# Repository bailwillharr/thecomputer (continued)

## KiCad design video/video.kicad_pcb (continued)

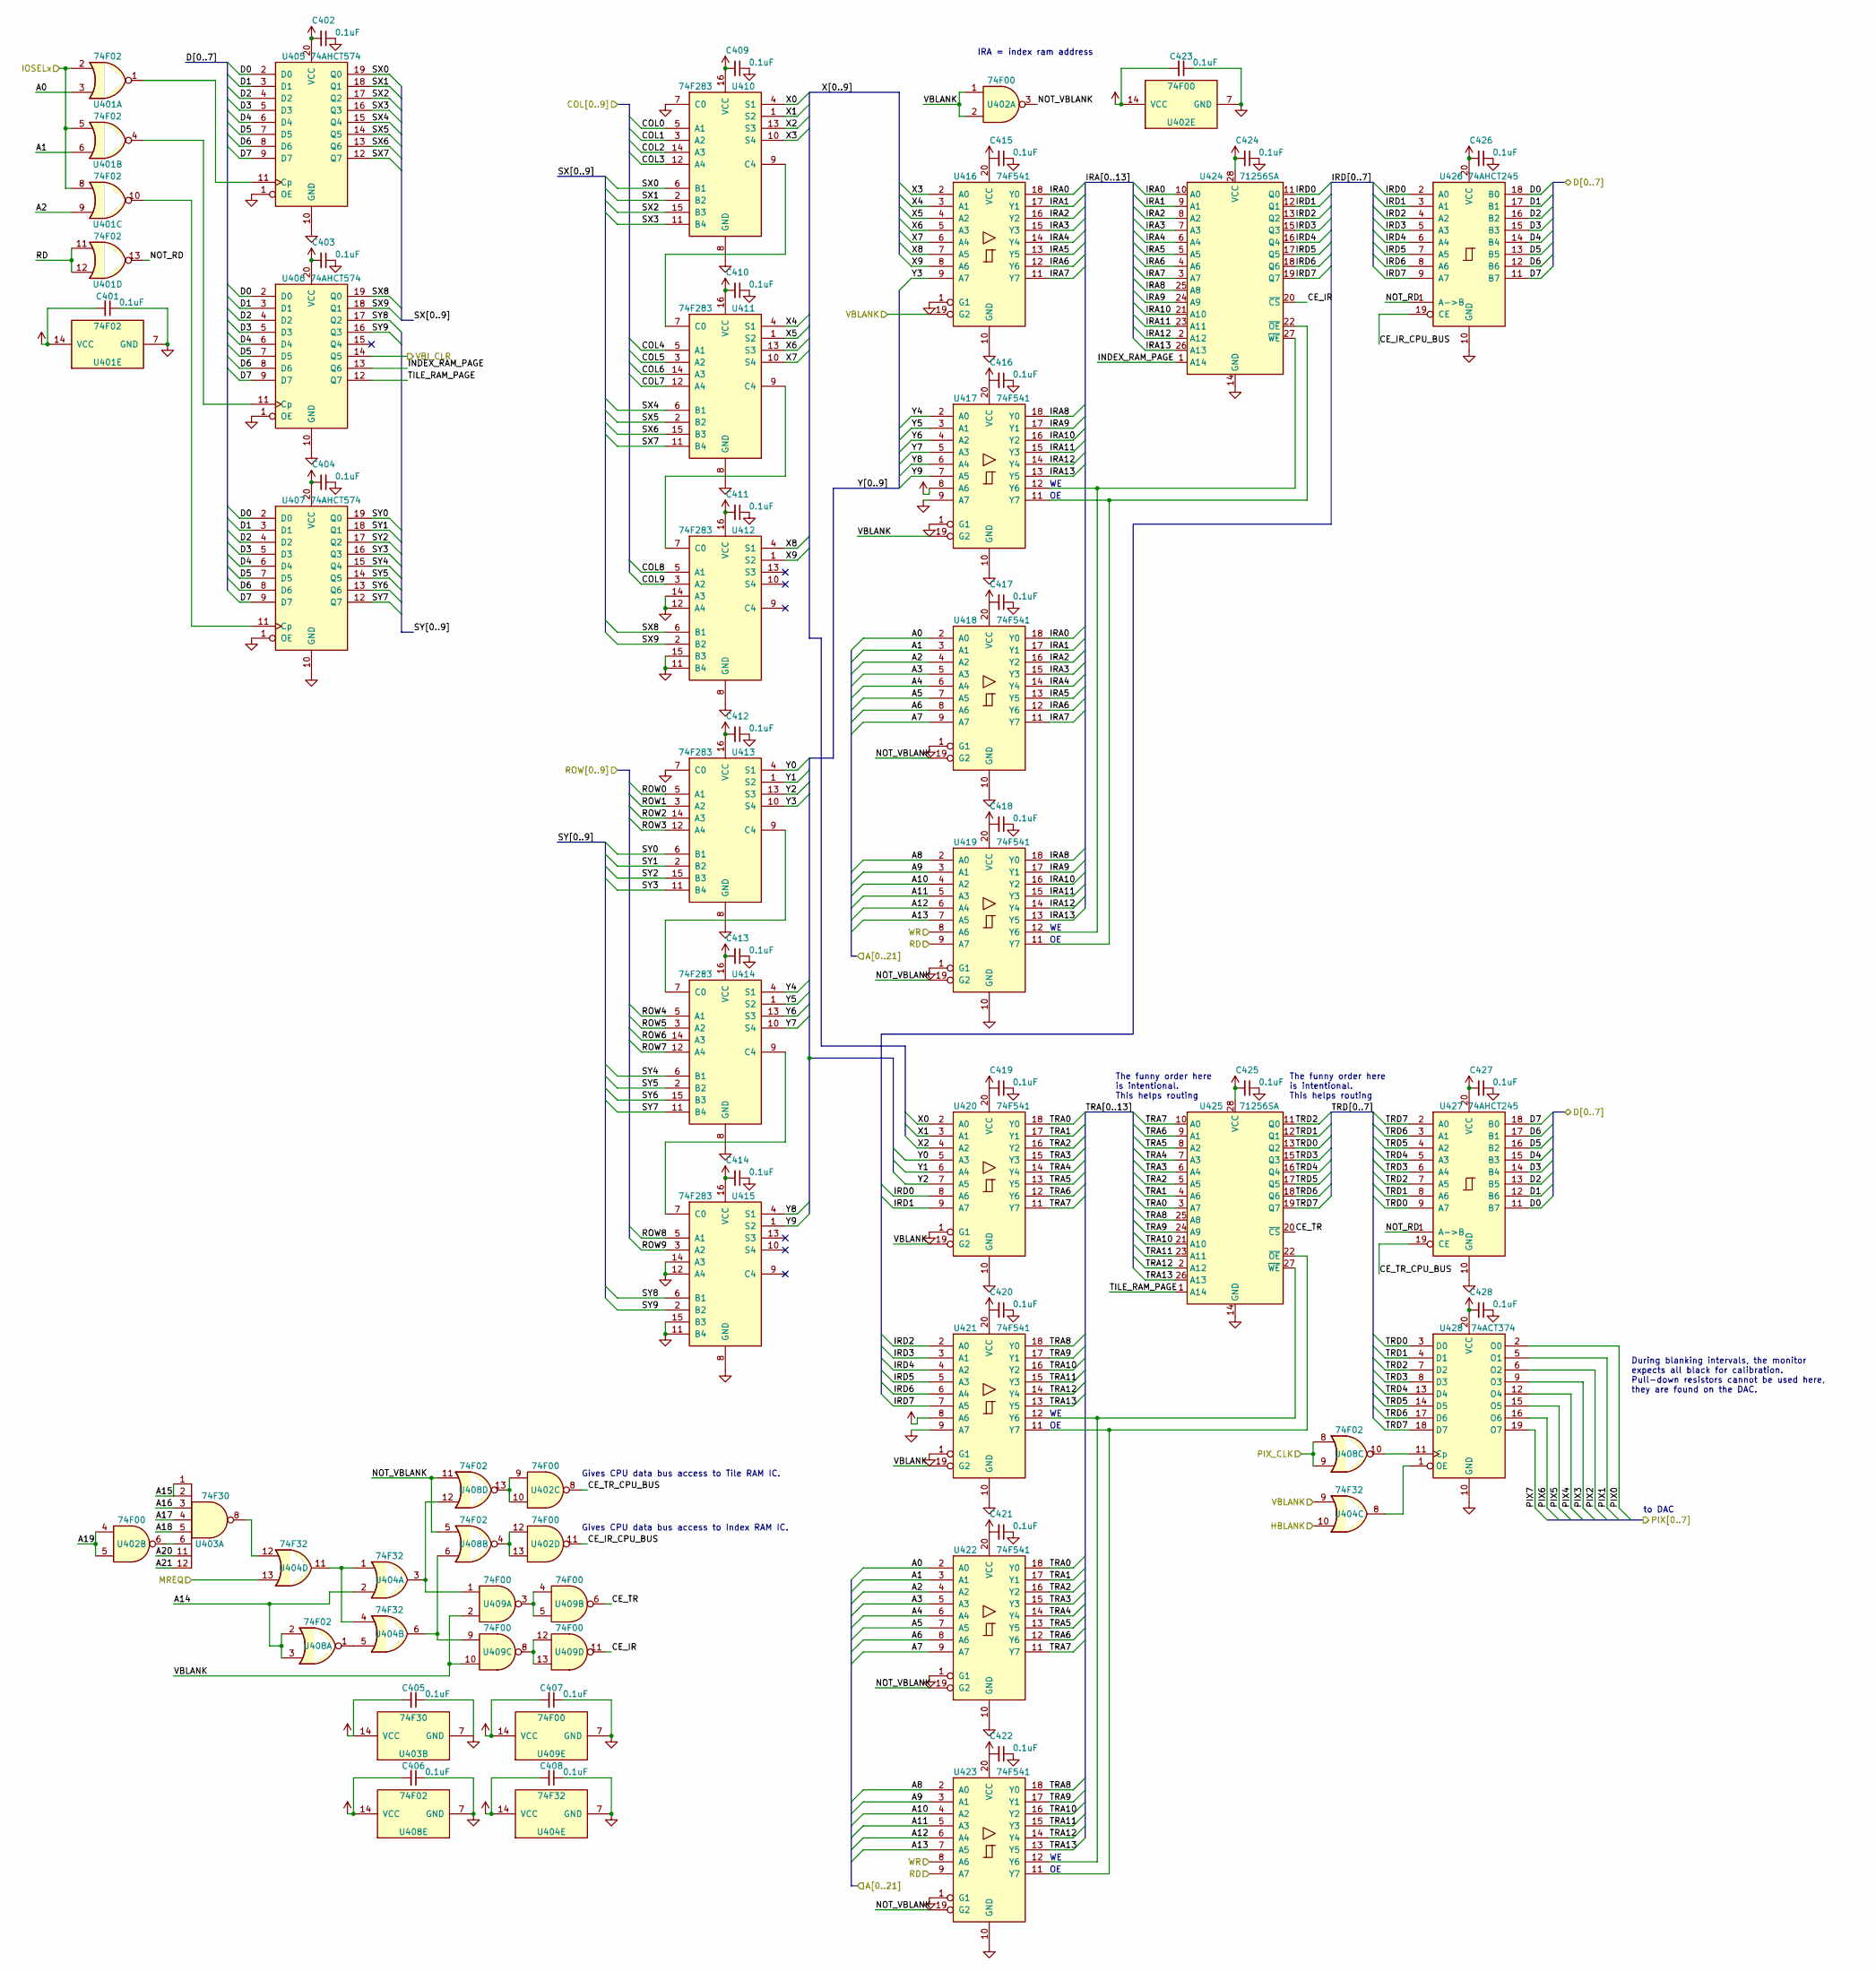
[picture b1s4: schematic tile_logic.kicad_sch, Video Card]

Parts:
C401, C402, C403, C404, C405, C406, C407, C408, C409, C410, C411, C412, C413, C414, C415, C416, C417, C418, C419, C420, C421, C422, C423, C424, C425, C426, C427, C428: 0.1uF; C_Disc_D5.0mm_W2.5mm_P2.50mm; Digikey Part No. 399-9859-1-ND
U401, U408: 74F02; DIP-14_W7.62mm_Socket; Digikey Part No. 296-3541-5-ND
U402, U409: 74F00; DIP-14_W7.62mm_Socket; Digikey Part No. 296-3539-5-ND
U403: 74F30; DIP-14_W7.62mm_Socket; Digikey Part No. 296-SN74F30N-ND
U404: 74F32; DIP-14_W7.62mm_Socket; Digikey Part No. 296-3583-5-ND
U405, U406, U407: 74AHCT574; DIP-20_W7.62mm_Socket; Digikey Part No. 296-4763-5-ND
U410, U411, U412, U413, U414, U415: 74F283; DIP-16_W7.62mm_Socket; Digikey Part No. 296-3580-5-ND
U416, U417, U418, U419, U420, U421, U422, U423: 74F541; DIP-20_W7.62mm_Socket; Digikey Part No. 296-3594-5-ND
U424, U425: 71256SA; DIP-28_W7.62mm_Socket; Digikey Part No. 800-3675-ND
U426, U427: 74AHCT245; DIP-20_W7.62mm_Socket; Digikey Part No. 296-1476-5-ND
U428: 74ACT374; DIP-20_W7.62mm_Socket; Digikey Part No. 296-33658-5-ND

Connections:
+5V: C401.2, C402.2, C403.2, C404.2, C405.2, C406.2, C407.2, C408.2, C409.2, C410.2, C411.2, C412.2, C413.2, C414.2, C415.2, C416.2, C417.2, C418.2, C419.2, C420.2, C421.2, C422.2, C423.2, C424.2, C425.2, C426.2, C427.2, C428.2, U401.14 (VCC), U402.14 (VCC), U403.14 (VCC), U404.14 (VCC), U405.20 (VCC), U406.20 (VCC), U407.20 (VCC), U408.14 (VCC), U409.14 (VCC), U410.16 (VCC), U411.16 (VCC), U412.16 (VCC), U413.16 (VCC), U414.16 (VCC), U415.16 (VCC), U416.20 (VCC), U417.8 (A6), U417.20 (VCC), U418.20 (VCC), U419.20 (VCC), U420.20 (VCC), U421.8 (A6), U421.20 (VCC), U422.20 (VCC), U423.20 (VCC), U424.28 (VCC), U425.28 (VCC), U426.20 (VCC), U427.20 (VCC), U428.20 (VCC); also elsewhere on the board
/A0: U401.3, U418.2 (A0), U422.2 (A0); also elsewhere on the board
/A1: U401.6, U418.3 (A1), U422.3 (A1); also elsewhere on the board
/A2: U401.9, U418.4 (A2), U422.4 (A2); also elsewhere on the board
/A3: U418.5 (A3), U422.5 (A3); also elsewhere on the board
/A4: U418.6 (A4), U422.6 (A4); also elsewhere on the board
/A5: U418.7 (A5), U422.7 (A5); also elsewhere on the board
/A6: U418.8 (A6), U422.8 (A6); also elsewhere on the board
/A7: U418.9 (A7), U422.9 (A7); also elsewhere on the board
/A8: U419.2 (A0), U423.2 (A0); also elsewhere on the board
/A9: U419.3 (A1), U423.3 (A1); also elsewhere on the board
/A10: U419.4 (A2), U423.4 (A2); also elsewhere on the board
/A11: U419.5 (A3), U423.5 (A3); also elsewhere on the board
/A12: U419.6 (A4), U423.6 (A4); also elsewhere on the board
/A13: U419.7 (A5), U423.7 (A5); also elsewhere on the board
/A14: U404.2, U408.2, U408.3; also elsewhere on the board
/A15: U403.1, U403.2; also elsewhere on the board
/A16: U403.3; also elsewhere on the board
/A17: U403.4; also elsewhere on the board
/A18: U403.5; also elsewhere on the board
/A19: U402.4, U402.5; also elsewhere on the board
/A20: U403.11; also elsewhere on the board
/A21: U403.12; also elsewhere on the board
/D0: U405.2 (D0), U406.2 (D0), U407.2 (D0), U426.18 (B0), U427.11 (B7); also elsewhere on the board
/D1: U405.3 (D1), U406.3 (D1), U407.3 (D1), U426.17 (B1), U427.12 (B6); also elsewhere on the board
/D2: U405.4 (D2), U406.4 (D2), U407.4 (D2), U426.16 (B2), U427.13 (B5); also elsewhere on the board
/D3: U405.5 (D3), U406.5 (D3), U407.5 (D3), U426.15 (B3), U427.14 (B4); also elsewhere on the board
/D4: U405.6 (D4), U406.6 (D4), U407.6 (D4), U426.14 (B4), U427.15 (B3); also elsewhere on the board
/D5: U405.7 (D5), U406.7 (D5), U407.7 (D5), U426.13 (B5), U427.16 (B2); also elsewhere on the board
/D6: U405.8 (D6), U406.8 (D6), U407.8 (D6), U426.12 (B6), U427.17 (B1); also elsewhere on the board
/D7: U405.9 (D7), U406.9 (D7), U407.9 (D7), U426.11 (B7), U427.18 (B0); also elsewhere on the board
/IOSELx: U401.2, U401.5, U401.8; also elsewhere on the board
/MREQ: U404.13; also elsewhere on the board
/PIX0: U428.2 (O0); also elsewhere on the board
/PIX1: U428.5 (O1); also elsewhere on the board
/PIX2: U428.6 (O2); also elsewhere on the board
/PIX3: U428.9 (O3); also elsewhere on the board
/PIX4: U428.12 (O4); also elsewhere on the board
/PIX5: U428.15 (O5); also elsewhere on the board
/PIX6: U428.16 (O6); also elsewhere on the board
/PIX7: U428.19 (O7); also elsewhere on the board
/PIX_CLK: U408.8, U408.9; also elsewhere on the board
/RD: U401.11, U401.12, U419.9 (A7), U423.9 (A7); also elsewhere on the board
/TILE_LOGIC/CE_IR: U409.11, U424.20 (~CS)
/TILE_LOGIC/CE_IR_CPU_BUS: U402.11, U426.19 (CE)
/TILE_LOGIC/CE_TR: U409.6, U425.20 (~CS)
/TILE_LOGIC/CE_TR_CPU_BUS: U402.8, U427.19 (CE)
/TILE_LOGIC/HBLANK: U404.10; also elsewhere on the board
/TILE_LOGIC/INDEX_RAM_PAGE: U406.13 (Q6), U424.1 (A14)
/TILE_LOGIC/IRA0: U416.18 (Y0), U418.18 (Y0), U424.10 (A0)
/TILE_LOGIC/IRA1: U416.17 (Y1), U418.17 (Y1), U424.9 (A1)
/TILE_LOGIC/IRA2: U416.16 (Y2), U418.16 (Y2), U424.8 (A2)
/TILE_LOGIC/IRA3: U416.15 (Y3), U418.15 (Y3), U424.7 (A3)
/TILE_LOGIC/IRA4: U416.14 (Y4), U418.14 (Y4), U424.6 (A4)
/TILE_LOGIC/IRA5: U416.13 (Y5), U418.13 (Y5), U424.5 (A5)
/TILE_LOGIC/IRA6: U416.12 (Y6), U418.12 (Y6), U424.4 (A6)
/TILE_LOGIC/IRA7: U416.11 (Y7), U418.11 (Y7), U424.3 (A7)
/TILE_LOGIC/IRA8: U417.18 (Y0), U419.18 (Y0), U424.25 (A8)
/TILE_LOGIC/IRA9: U417.17 (Y1), U419.17 (Y1), U424.24 (A9)
/TILE_LOGIC/IRA10: U417.16 (Y2), U419.16 (Y2), U424.21 (A10)
/TILE_LOGIC/IRA11: U417.15 (Y3), U419.15 (Y3), U424.23 (A11)
/TILE_LOGIC/IRA12: U417.14 (Y4), U419.14 (Y4), U424.2 (A12)
/TILE_LOGIC/IRA13: U417.13 (Y5), U419.13 (Y5), U424.26 (A13)
/TILE_LOGIC/IRD0: U420.8 (A6), U424.11 (Q0), U426.2 (A0)
/TILE_LOGIC/IRD1: U420.9 (A7), U424.12 (Q1), U426.3 (A1)
/TILE_LOGIC/IRD2: U421.2 (A0), U424.13 (Q2), U426.4 (A2)
/TILE_LOGIC/IRD3: U421.3 (A1), U424.15 (Q3), U426.5 (A3)
/TILE_LOGIC/IRD4: U421.4 (A2), U424.16 (Q4), U426.6 (A4)
/TILE_LOGIC/IRD5: U421.5 (A3), U424.17 (Q5), U426.7 (A5)
/TILE_LOGIC/IRD6: U421.6 (A4), U424.18 (Q6), U426.8 (A6)
/TILE_LOGIC/IRD7: U421.7 (A5), U424.19 (Q7), U426.9 (A7)
/TILE_LOGIC/NOT_RD: U401.13, U426.1 (A->B), U427.1 (A->B)
/TILE_LOGIC/NOT_VBLANK: U402.3, U408.5, U408.11, U418.19 (G2), U419.19 (G2), U422.19 (G2), U423.19 (G2)
/TILE_LOGIC/SX0: U405.19 (Q0), U410.6 (B1)
/TILE_LOGIC/SX1: U405.18 (Q1), U410.2 (B2)
/TILE_LOGIC/SX2: U405.17 (Q2), U410.15 (B3)
/TILE_LOGIC/SX3: U405.16 (Q3), U410.11 (B4)
/TILE_LOGIC/SX4: U405.15 (Q4), U411.6 (B1)
/TILE_LOGIC/SX5: U405.14 (Q5), U411.2 (B2)
/TILE_LOGIC/SX6: U405.13 (Q6), U411.15 (B3)
/TILE_LOGIC/SX7: U405.12 (Q7), U411.11 (B4)
/TILE_LOGIC/SX8: U406.19 (Q0), U412.6 (B1)
/TILE_LOGIC/SX9: U406.18 (Q1), U412.2 (B2)
/TILE_LOGIC/SY0: U407.19 (Q0), U413.6 (B1)
/TILE_LOGIC/SY1: U407.18 (Q1), U413.2 (B2)
/TILE_LOGIC/SY2: U407.17 (Q2), U413.15 (B3)
/TILE_LOGIC/SY3: U407.16 (Q3), U413.11 (B4)
/TILE_LOGIC/SY4: U407.15 (Q4), U414.6 (B1)
/TILE_LOGIC/SY5: U407.14 (Q5), U414.2 (B2)
/TILE_LOGIC/SY6: U407.13 (Q6), U414.15 (B3)
/TILE_LOGIC/SY7: U407.12 (Q7), U414.11 (B4)
/TILE_LOGIC/SY8: U406.17 (Q2), U415.6 (B1)
/TILE_LOGIC/SY9: U406.16 (Q3), U415.2 (B2)
/TILE_LOGIC/TILE_RAM_PAGE: U406.12 (Q7), U425.1 (A14)
/TILE_LOGIC/TRA0: U420.18 (Y0), U422.18 (Y0), U425.3 (A7)
/TILE_LOGIC/TRA1: U420.17 (Y1), U422.17 (Y1), U425.4 (A6)
/TILE_LOGIC/TRA2: U420.16 (Y2), U422.16 (Y2), U425.5 (A5)
/TILE_LOGIC/TRA3: U420.15 (Y3), U422.15 (Y3), U425.6 (A4)
/TILE_LOGIC/TRA4: U420.14 (Y4), U422.14 (Y4), U425.7 (A3)
/TILE_LOGIC/TRA5: U420.13 (Y5), U422.13 (Y5), U425.8 (A2)
/TILE_LOGIC/TRA6: U420.12 (Y6), U422.12 (Y6), U425.9 (A1)
/TILE_LOGIC/TRA7: U420.11 (Y7), U422.11 (Y7), U425.10 (A0)
/TILE_LOGIC/TRA8: U421.18 (Y0), U423.18 (Y0), U425.25 (A8)
/TILE_LOGIC/TRA9: U421.17 (Y1), U423.17 (Y1), U425.24 (A9)
/TILE_LOGIC/TRA10: U421.16 (Y2), U423.16 (Y2), U425.21 (A10)
/TILE_LOGIC/TRA11: U421.15 (Y3), U423.15 (Y3), U425.23 (A11)
/TILE_LOGIC/TRA12: U421.14 (Y4), U423.14 (Y4), U425.2 (A12)
/TILE_LOGIC/TRA13: U421.13 (Y5), U423.13 (Y5), U425.26 (A13)
/TILE_LOGIC/TRD0: U425.13 (Q2), U427.9 (A7), U428.3 (D0)
/TILE_LOGIC/TRD1: U425.12 (Q1), U427.8 (A6), U428.4 (D1)
/TILE_LOGIC/TRD2: U425.11 (Q0), U427.7 (A5), U428.7 (D2)
/TILE_LOGIC/TRD3: U425.15 (Q3), U427.6 (A4), U428.8 (D3)
/TILE_LOGIC/TRD4: U425.16 (Q4), U427.5 (A3), U428.13 (D4)
/TILE_LOGIC/TRD5: U425.17 (Q5), U427.4 (A2), U428.14 (D5)
/TILE_LOGIC/TRD6: U425.18 (Q6), U427.3 (A1), U428.17 (D6)
/TILE_LOGIC/TRD7: U425.19 (Q7), U427.2 (A0), U428.18 (D7)
/TILE_LOGIC/VBI_CLR: U406.14 (Q5); also elsewhere on the board
/TILE_LOGIC/VBLANK: U402.1, U402.2, U404.9, U409.2, U409.10, U416.19 (G2), U417.19 (G2), U420.19 (G2), U421.19 (G2); also elsewhere on the board
/TILE_LOGIC/X0: U410.4 (S1), U420.2 (A0)
/TILE_LOGIC/X1: U410.1 (S2), U420.3 (A1)
/TILE_LOGIC/X2: U410.13 (S3), U420.4 (A2)
/TILE_LOGIC/X3: U410.10 (S4), U416.2 (A0)
/TILE_LOGIC/X4: U411.4 (S1), U416.3 (A1)
/TILE_LOGIC/X5: U411.1 (S2), U416.4 (A2)
/TILE_LOGIC/X6: U411.13 (S3), U416.5 (A3)
/TILE_LOGIC/X7: U411.10 (S4), U416.6 (A4)
/TILE_LOGIC/X8: U412.4 (S1), U416.7 (A5)
/TILE_LOGIC/X9: U412.1 (S2), U416.8 (A6)
/TILE_LOGIC/Y0: U413.4 (S1), U420.5 (A3)
/TILE_LOGIC/Y1: U413.1 (S2), U420.6 (A4)
/TILE_LOGIC/Y2: U413.13 (S3), U420.7 (A5)
/TILE_LOGIC/Y3: U413.10 (S4), U416.9 (A7)
/TILE_LOGIC/Y4: U414.4 (S1), U417.2 (A0)
/TILE_LOGIC/Y5: U414.1 (S2), U417.3 (A1)
/TILE_LOGIC/Y6: U414.13 (S3), U417.4 (A2)
/TILE_LOGIC/Y7: U414.10 (S4), U417.5 (A3)
/TILE_LOGIC/Y8: U415.4 (S1), U417.6 (A4)
/TILE_LOGIC/Y9: U415.1 (S2), U417.7 (A5)
/TIMING/COL0: U410.5 (A1); also elsewhere on the board
/TIMING/COL1: U410.3 (A2); also elsewhere on the board
/TIMING/COL2: U410.14 (A3); also elsewhere on the board
/TIMING/COL3: U410.12 (A4); also elsewhere on the board
/TIMING/COL4: U411.5 (A1); also elsewhere on the board
/TIMING/COL5: U411.3 (A2); also elsewhere on the board
/TIMING/COL6: U411.14 (A3); also elsewhere on the board
/TIMING/COL7: U411.12 (A4); also elsewhere on the board
/TIMING/COL8: U412.5 (A1); also elsewhere on the board
/TIMING/COL9: U412.3 (A2); also elsewhere on the board
/TIMING/ROW0: U413.5 (A1); also elsewhere on the board
/TIMING/ROW1: U413.3 (A2); also elsewhere on the board
/TIMING/ROW2: U413.14 (A3); also elsewhere on the board
/TIMING/ROW3: U413.12 (A4); also elsewhere on the board
/TIMING/ROW4: U414.5 (A1); also elsewhere on the board
/TIMING/ROW5: U414.3 (A2); also elsewhere on the board
/TIMING/ROW6: U414.14 (A3); also elsewhere on the board
/TIMING/ROW7: U414.12 (A4); also elsewhere on the board
/TIMING/ROW8: U415.5 (A1); also elsewhere on the board
/TIMING/ROW9: U415.3 (A2); also elsewhere on the board
/WR: U419.8 (A6), U423.8 (A6); also elsewhere on the board
GND: C401.1, C402.1, C403.1, C404.1, C405.1, C406.1, C407.1, C408.1, C409.1, C410.1, C411.1, C412.1, C413.1, C414.1, C415.1, C416.1, C417.1, C418.1, C419.1, C420.1, C421.1, C422.1, C423.1, C424.1, C425.1, C426.1, C427.1, C428.1, U401.7 (GND), U402.7 (GND), U403.7 (GND), U404.7 (GND), U405.1 (OE), U405.10 (GND), U406.1 (OE), U406.10 (GND), U407.1 (OE), U407.10 (GND), U408.7 (GND), U409.7 (GND), U410.7 (C0), U410.8 (GND), U411.8 (GND), U412.8 (GND), U412.11 (B4), U412.12 (A4), U412.14 (A3), U412.15 (B3), U413.7 (C0), U413.8 (GND), U414.8 (GND), U415.8 (GND), U415.11 (B4), U415.12 (A4), U415.14 (A3), U415.15 (B3), U416.1 (G1), U416.10 (GND), U417.1 (G1), U417.9 (A7), U417.10 (GND), U418.1 (G1), U418.10 (GND), U419.1 (G1), U419.10 (GND), U420.1 (G1), U420.10 (GND), U421.1 (G1), U421.9 (A7), U421.10 (GND), U422.1 (G1), U422.10 (GND), U423.1 (G1), U423.10 (GND), U424.14 (GND), U425.14 (GND), U426.10 (GND), U427.10 (GND), U428.10 (GND); also elsewhere on the board
unnamed: U402.6, U403.6
unnamed: U402.9, U402.10, U408.13
unnamed: U402.12, U402.13, U408.4
unnamed: U403.8, U404.12
unnamed: U404.1, U404.4, U404.11
unnamed: U404.3, U408.12, U409.1
unnamed: U404.5, U408.1
unnamed: U404.6, U408.6, U409.9
unnamed: U401.1, U405.11 (Cp)
unnamed: U401.4, U406.11 (Cp)
unnamed: U401.10, U407.11 (Cp)
unnamed: U409.3, U409.4, U409.5
unnamed: U409.8, U409.12, U409.13
unnamed: U410.9 (C4), U411.7 (C0)
unnamed: U411.9 (C4), U412.7 (C0)
unnamed: U413.9 (C4), U414.7 (C0)
unnamed: U414.9 (C4), U415.7 (C0)
unnamed: U417.12 (Y6), U419.12 (Y6), U424.27 (~WE)
unnamed: U417.11 (Y7), U419.11 (Y7), U424.22 (~OE)
unnamed: U421.12 (Y6), U423.12 (Y6), U425.27 (~WE)
unnamed: U421.11 (Y7), U423.11 (Y7), U425.22 (~OE)
unnamed: U408.10, U428.11 (Cp)
unnamed: U404.8, U428.1 (OE)

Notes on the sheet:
During blanking intervals, the monitor expects all black for calibration. Pull-down resistors cannot be used here, they are found on the DAC.
to DAC
The funny order here is intentional. This helps routing
Gives CPU data bus access to Index RAM IC.
IRA = index ram address
Gives CPU data bus access to Tile RAM IC.

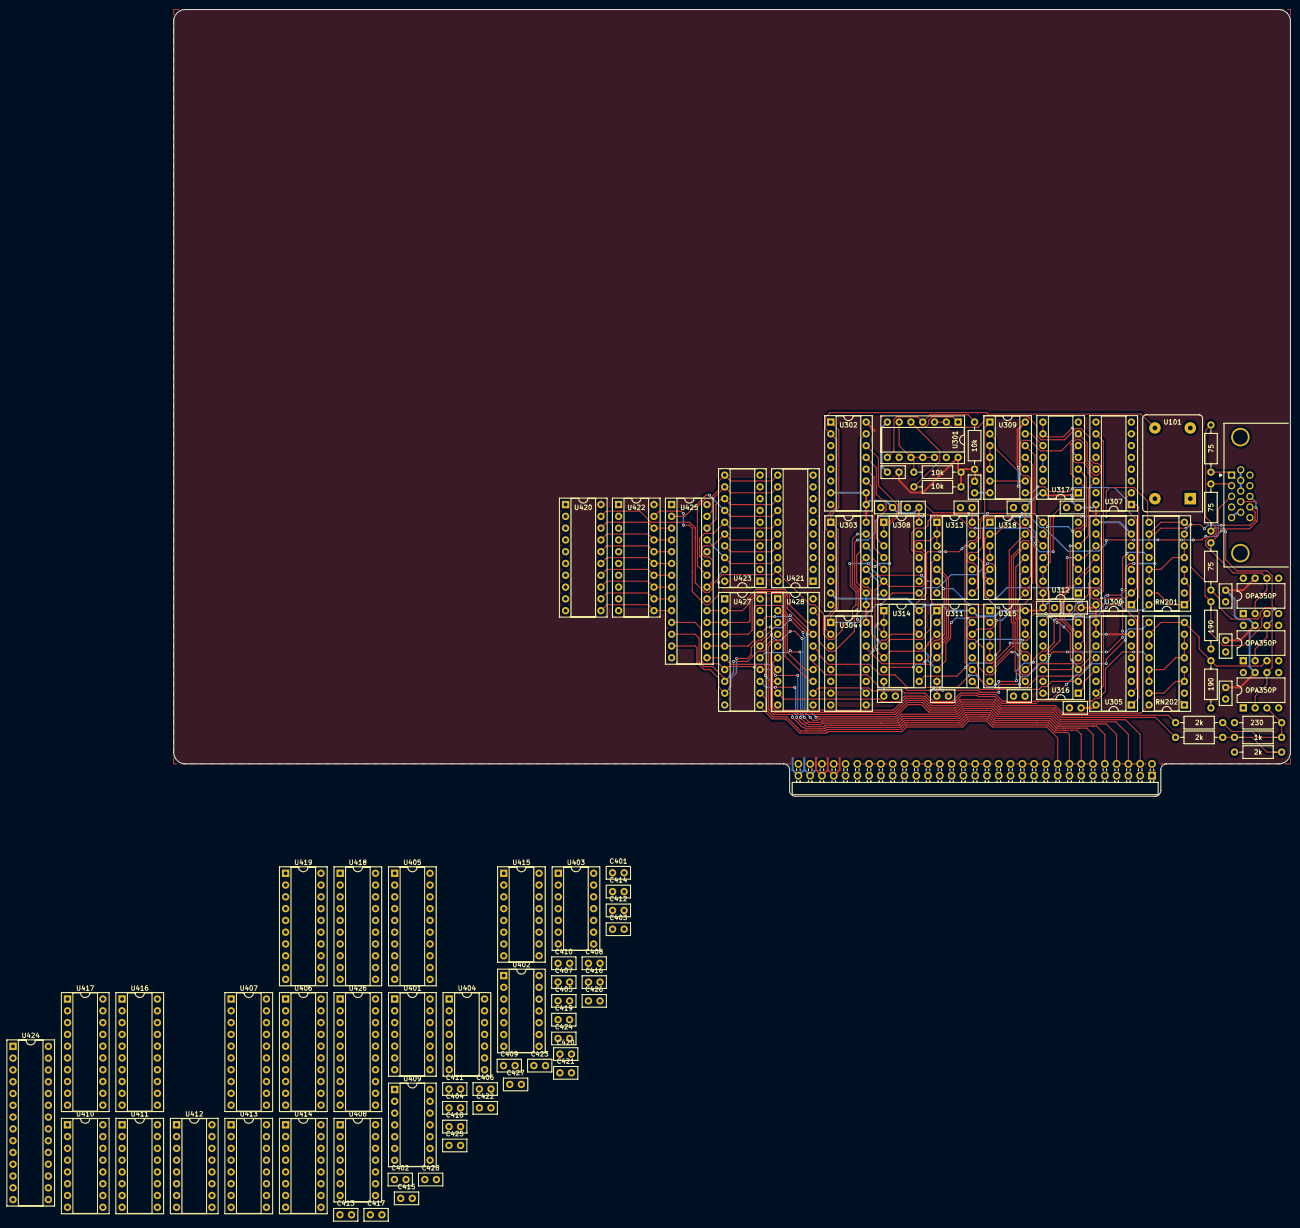
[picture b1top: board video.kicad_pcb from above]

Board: 2 copper layers, 240.7 x 169.5 mm, 110 parts (0 on the bottom side), 232 nets.

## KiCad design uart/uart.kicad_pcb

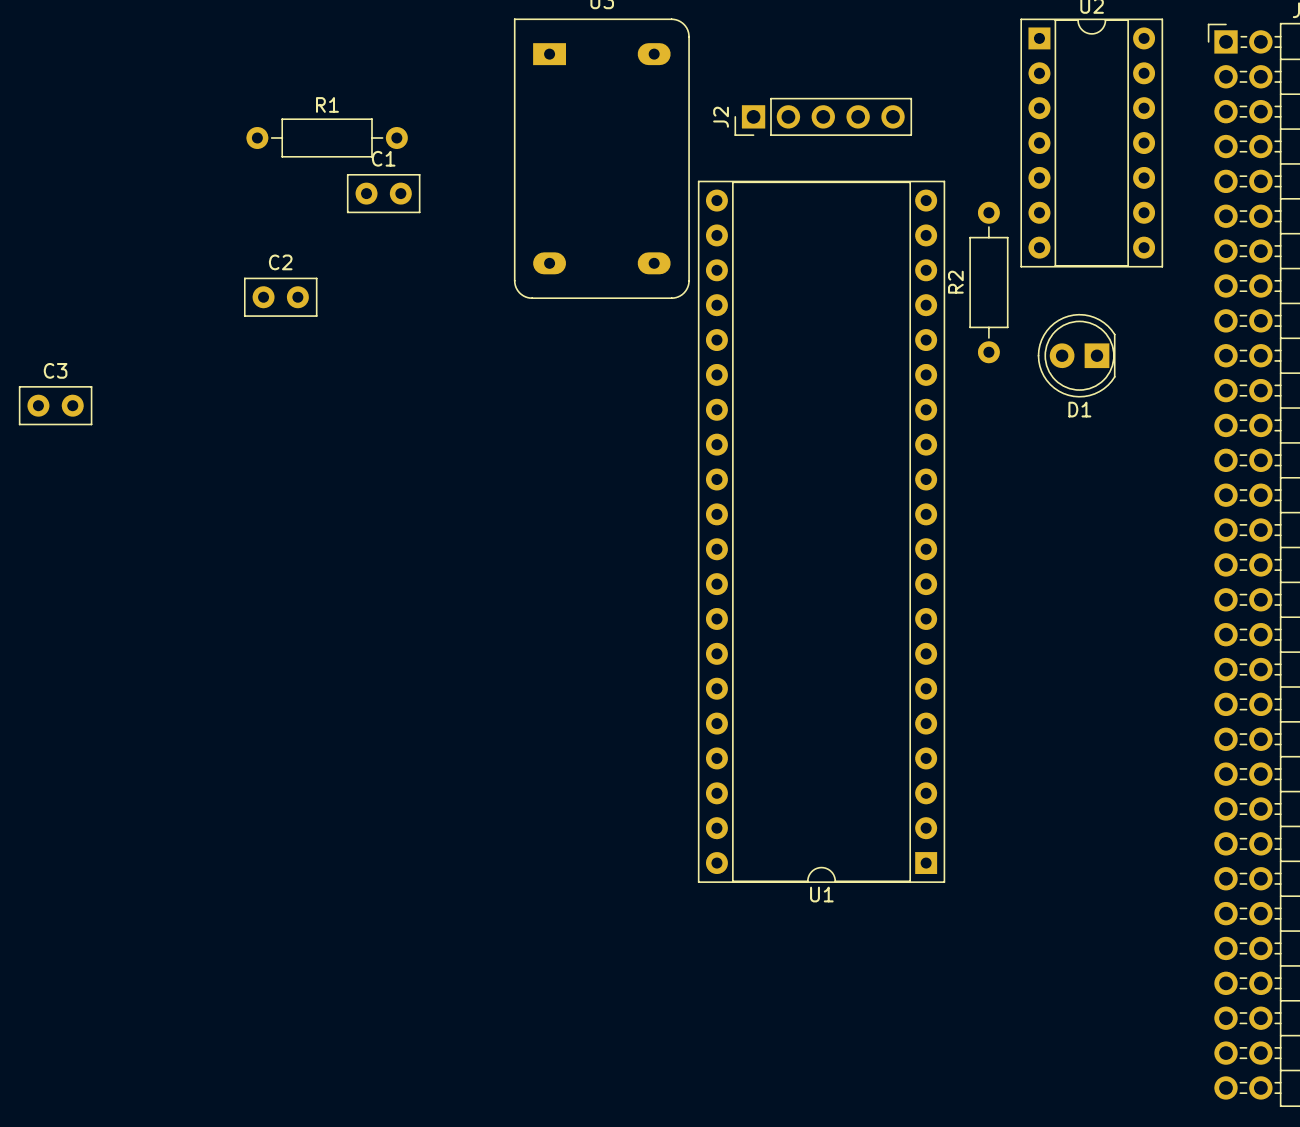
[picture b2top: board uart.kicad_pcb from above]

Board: 2 copper layers, 11 parts (0 on the bottom side), 28 nets, no tracks yet.

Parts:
C1, C2, C3: 0.1µF; C_Disc_D5.0mm_W2.5mm_P2.50mm
D1: LED; LED_D5.0mm
J1: 2x31 Connector Cardside; PinHeader_2x31_P2.54mm_Horizontal
J2: 1x5 Connector Female; PinHeader_1x05_P2.54mm_Vertical
R1: 10k; R_Axial_DIN0207_L6.3mm_D2.5mm_P10.16mm_Horizontal
R2: 330; R_Axial_DIN0207_L6.3mm_D2.5mm_P10.16mm_Horizontal
U1: TL16C550CN; DIP-40_W15.24mm_Socket
U2: 74LS05; DIP-14_W7.62mm_Socket
U3: 16MHz; DIP-14_CornersOnly_Crystal

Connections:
+5V: C1.2, C2.2, C3.2, J1.56, J1.58, R1.1, R2.1, U1.12, U1.13, U1.40, U2.14, U3.1, U3.14
/A0: J1.61, U1.28
/A1: J1.59, U1.27
/A2: J1.57, U1.26
/CTS: J2.1, U1.36
/D0: J1.17, U1.1
/D1: J1.15, U1.2
/D2: J1.13, U1.3
/D3: J1.11, U1.4
/D4: J1.9, U1.5
/D5: J1.7, U1.6
/D6: J1.5, U1.7
/D7: J1.3, U1.8
/HALT: J1.10, U2.5
/INT: J1.50, U2.2
/IOSELx: J1.30, U1.14
/RD: J1.32, U1.21
/RST: J1.4, U2.3
/RTS: J2.2, U1.32
/RX: J2.4, U1.10
/TX: J2.3, U1.11
/WR: J1.34, U1.18
GND: C1.1, C2.1, C3.1, D1.1, J1.60, J1.62, J2.5, U1.19, U1.20, U1.22, U1.25, U1.37, U1.38, U1.39, U2.7, U2.9, U2.11, U2.13, U3.7
unnamed: D1.2, R2.2, U2.6
unnamed: R1.2, U1.35, U2.4
unnamed: U1.9, U1.15
unnamed: U1.16, U3.8
unnamed: U1.30, U2.1

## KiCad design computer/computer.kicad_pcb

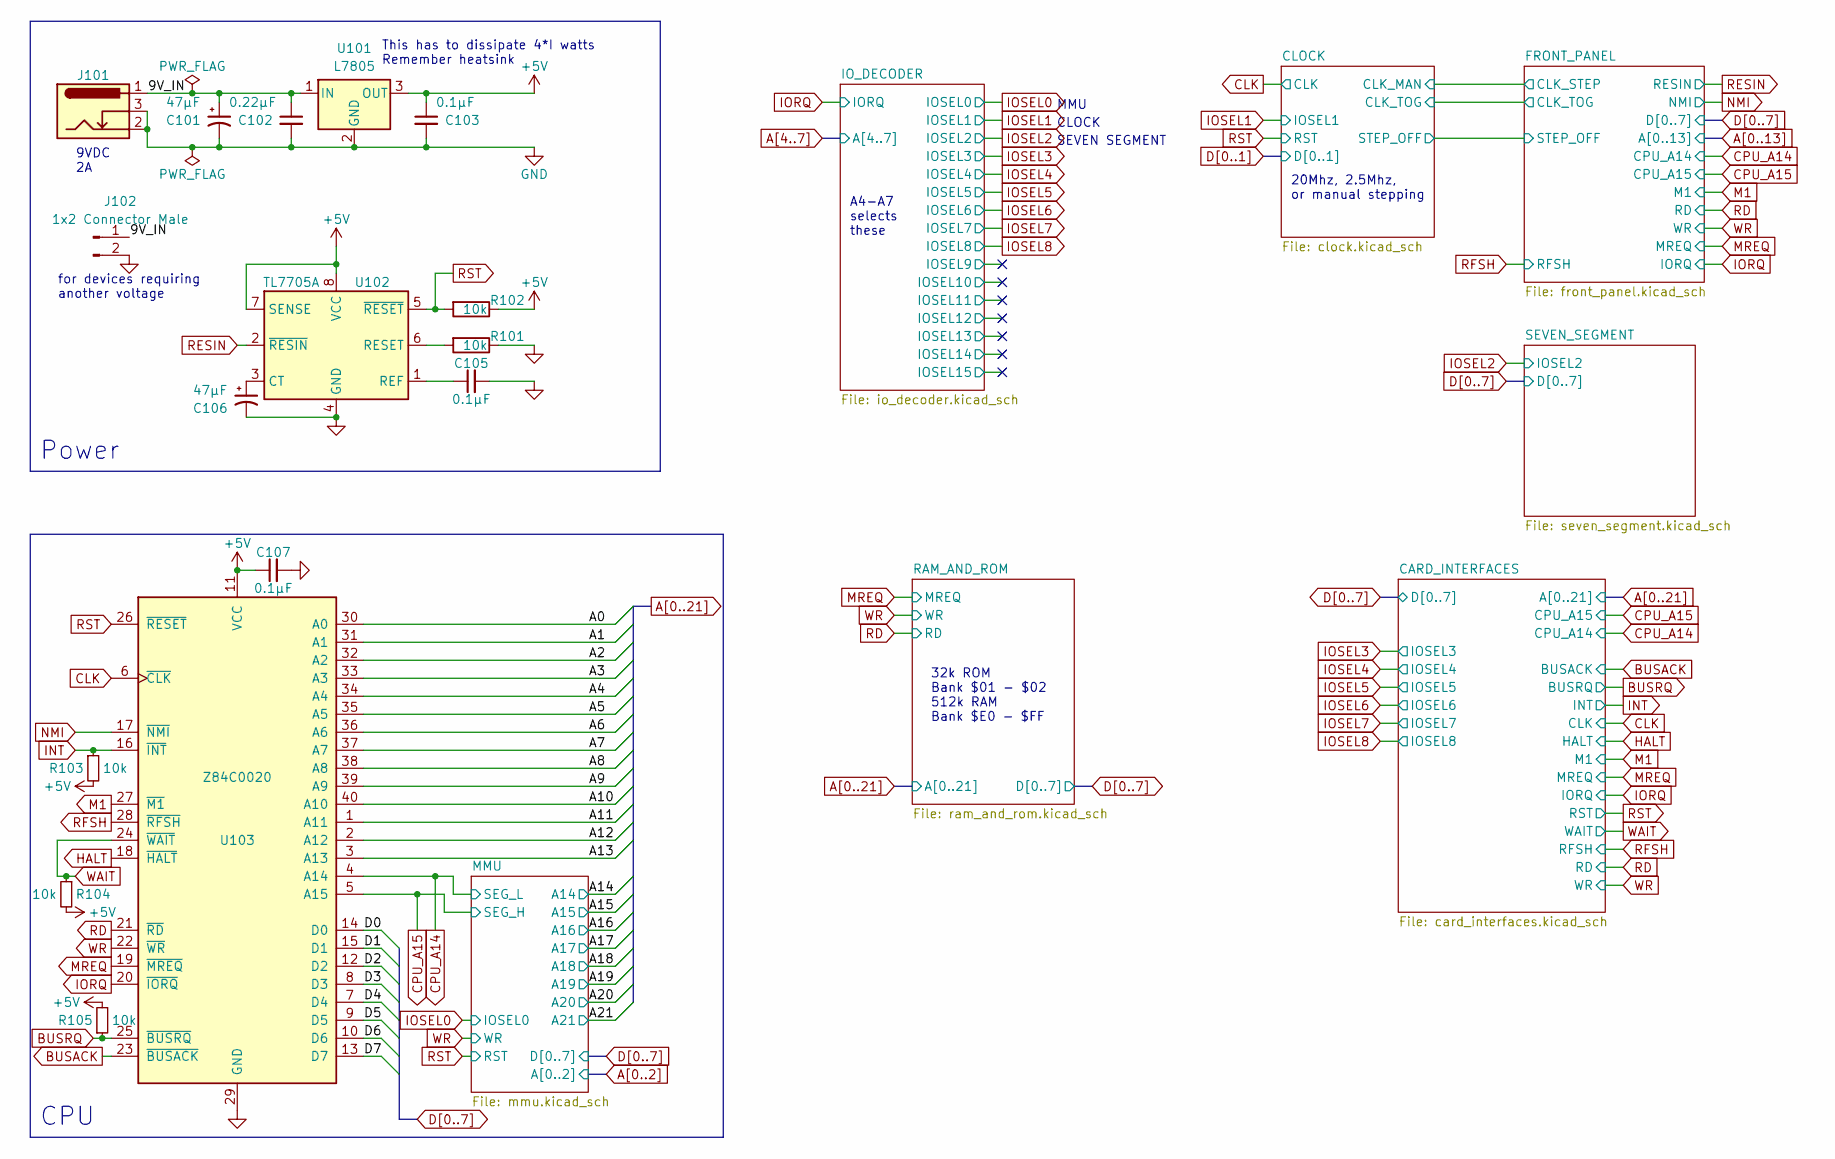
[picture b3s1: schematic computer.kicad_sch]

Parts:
C101, C106: 47µF; CP_Radial_D5.0mm_P2.50mm
C102: 0.22µF; C_Disc_D5.0mm_W2.5mm_P2.50mm
C103, C105, C107: 0.1µF; C_Disc_D5.0mm_W2.5mm_P2.50mm
J101: Barrel_Jack_Switch; BarrelJack_Horizontal
J102: 1x2 Connector Male; PinHeader_1x02_P2.54mm_Vertical
R101, R102, R103, R104, R105: 10k; R_Axial_DIN0207_L6.3mm_D2.5mm_P10.16mm_Horizontal
U101: L7805; TO-220-3_Vertical
U102: TL7705A; DIP-8_W7.62mm_Socket_LongPads
U103: Z84C0020; DIP-40_W15.24mm_Socket_LongPads

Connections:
+5V: C103.1, C107.1, R102.1, R103.2, R104.2, R105.2, U101.3 (OUT), U102.7 (SENSE), U102.8 (VCC), U103.11 (VCC); also elsewhere on the board
/9V_IN: C101.1, C102.1, J101.1, J102.1, U101.1 (IN)
A0: U103.30 (A0); also elsewhere on the board
A1: U103.31 (A1); also elsewhere on the board
A2: U103.32 (A2); also elsewhere on the board
A3: U103.33 (A3); also elsewhere on the board
A4: U103.34 (A4); also elsewhere on the board
A5: U103.35 (A5); also elsewhere on the board
A6: U103.36 (A6); also elsewhere on the board
A7: U103.37 (A7); also elsewhere on the board
A8: U103.38 (A8); also elsewhere on the board
A9: U103.39 (A9); also elsewhere on the board
A10: U103.40 (A10); also elsewhere on the board
A11: U103.1 (A11); also elsewhere on the board
A12: U103.2 (A12); also elsewhere on the board
A13: U103.3 (A13); also elsewhere on the board
BUSACK: U103.23 (~BUSACK); also elsewhere on the board
BUSRQ: R105.1, U103.25 (~BUSRQ); also elsewhere on the board
CLK: U103.6 (~CLK); also elsewhere on the board
CPU_A14: U103.4 (A14); also elsewhere on the board
CPU_A15: U103.5 (A15); also elsewhere on the board
D0: U103.14 (D0); also elsewhere on the board
D1: U103.15 (D1); also elsewhere on the board
D2: U103.12 (D2); also elsewhere on the board
D3: U103.8 (D3); also elsewhere on the board
D4: U103.7 (D4); also elsewhere on the board
D5: U103.9 (D5); also elsewhere on the board
D6: U103.10 (D6); also elsewhere on the board
D7: U103.13 (D7); also elsewhere on the board
GND: C101.2, C102.2, C103.2, C105.2, C106.2, C107.2, J101.2, J101.3, J102.2, R101.1, U101.2 (GND), U102.4 (GND), U103.29 (GND); also elsewhere on the board
HALT: U103.18 (~HALT); also elsewhere on the board
INT: R103.1, U103.16 (~INT); also elsewhere on the board
IORQ: U103.20 (~IORQ); also elsewhere on the board
M1: U103.27 (~M1); also elsewhere on the board
MREQ: U103.19 (~MREQ); also elsewhere on the board
NMI: U103.17 (~NMI); also elsewhere on the board
unnamed: C105.1, U102.1 (REF)
unnamed: C106.1, U102.3 (CT)
unnamed: R101.2, U102.6 (RESET)
RD: U103.21 (~RD); also elsewhere on the board
RESIN: U102.2 (~RESIN); also elsewhere on the board
RFSH: U103.28 (~RFSH); also elsewhere on the board
RST: R102.2, U102.5 (~RESET), U103.26 (~RESET); also elsewhere on the board
WAIT: R104.1, U103.24 (~WAIT); also elsewhere on the board
WR: U103.22 (~WR); also elsewhere on the board

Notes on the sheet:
for devices requiring another voltage
Power
A4-A7 selects these
This has to dissipate 4*I watts Remember heatsink
9VDC 2A
CLOCK
MMU
20Mhz, 2.5Mhz, or manual stepping
SEVEN SEGMENT
CPU
32k ROM Bank $01 - $02 512k RAM Bank $E0 - $FF

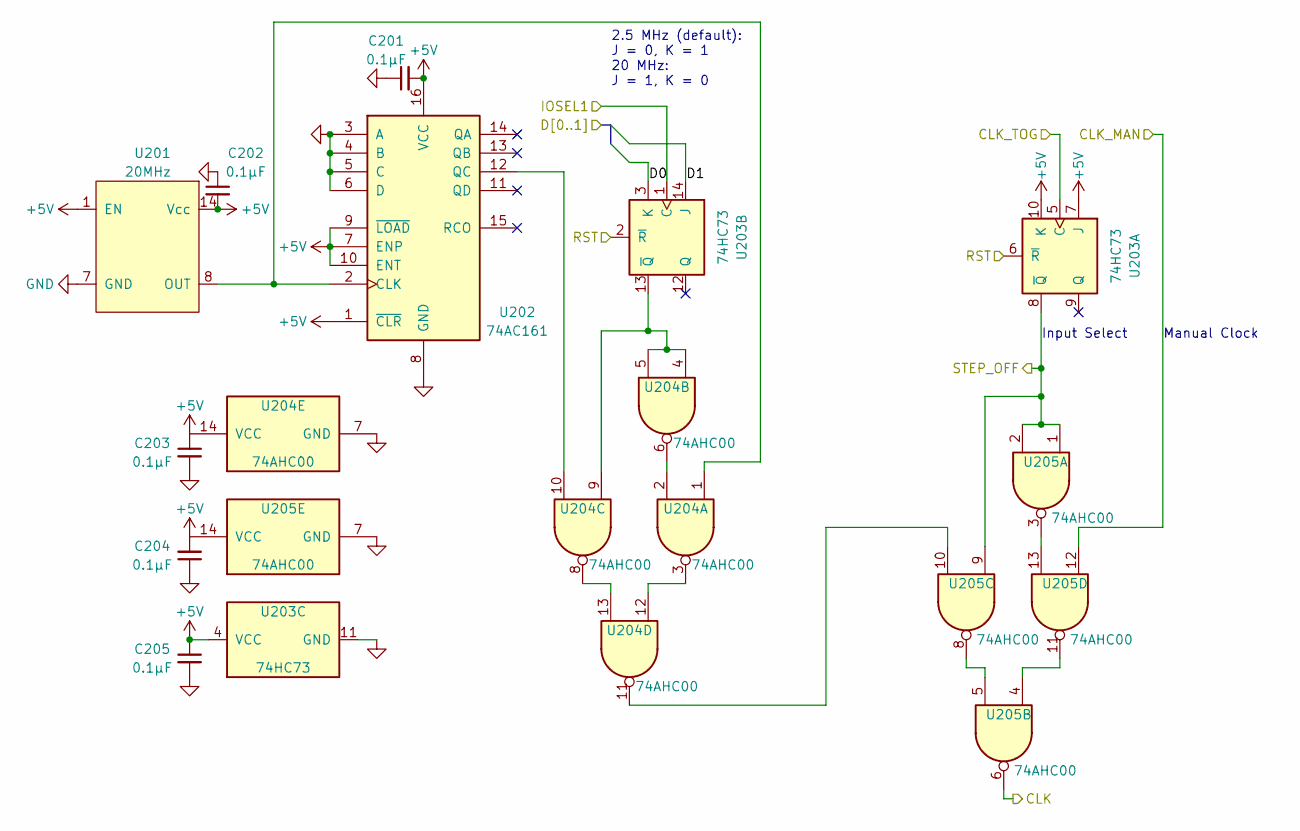
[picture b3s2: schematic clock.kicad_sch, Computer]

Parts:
C201, C202, C203, C204, C205: 0.1µF; C_Disc_D5.0mm_W2.5mm_P2.50mm
U201: 20MHz; DIP-14_W7.62mm_Socket_LongPads
U202: 74AC161; DIP-16_W7.62mm_Socket_LongPads
U203: 74HC73; DIP-14_W7.62mm_Socket_LongPads
U204, U205: 74AHC00; DIP-14_W7.62mm_Socket_LongPads

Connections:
+5V: C201.2, C202.2, C203.1, C204.2, C205.1, U201.1 (EN), U201.14 (Vcc), U202.1 (~CLR), U202.7 (ENP), U202.9 (~LOAD), U202.10 (ENT), U202.16 (VCC), U203.4 (VCC), U203.7 (J), U203.10 (K), U204.14 (VCC), U205.14 (VCC); also elsewhere on the board
/CLOCK/CLK_MAN: U205.12; also elsewhere on the board
/CLOCK/CLK_TOG: U203.5 (C); also elsewhere on the board
/CLOCK/STEP_OFF: U203.8 (~Q), U205.1, U205.2, U205.9; also elsewhere on the board
CLK: U205.6; also elsewhere on the board
D0: U203.3 (K); also elsewhere on the board
D1: U203.14 (J); also elsewhere on the board
GND: C201.1, C202.1, C203.2, C204.1, C205.2, U201.7 (GND), U202.3 (A), U202.4 (B), U202.5 (C), U202.6 (D), U202.8 (GND), U203.11 (GND), U204.7 (GND), U205.7 (GND); also elsewhere on the board
IOSEL1: U203.1 (C); also elsewhere on the board
unnamed: U201.8 (OUT), U202.2 (CLK), U204.1
unnamed: U202.12 (QC), U204.10
unnamed: U203.13 (~Q), U204.4, U204.5, U204.9
unnamed: U204.2, U204.6
unnamed: U204.11, U205.10
unnamed: U204.3, U204.12
unnamed: U204.8, U204.13
unnamed: U205.5, U205.8
unnamed: U205.4, U205.11
unnamed: U205.3, U205.13
RST: U203.2 (~R), U203.6 (~R); also elsewhere on the board

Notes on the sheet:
Manual Clock
2.5 MHz (default): J = 0, K = 1 20 MHz: J = 1, K = 0
Input Select
